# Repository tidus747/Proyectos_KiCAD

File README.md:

# Proyectos KiCAD
>Proyectos realizados en KiCAD a modo de tutoriales en Piensa 3D.

En este repositorio se almacenarán todos los proyectos para KiCAD desarrollados en Piensa 3D. Puedes encontrar todo lo necesario dentro de las carpetas con el nombre de cada uno de los proyectos. Recuerda que en si quieres subir tu proyecto a este repositorio no tienes más que enviar un mail a piensa3d.dudas@gmail.com.

## Herramientas utilizadas

Las herramientas utilizadas durante el desarrollo de los tutoriales han sido las siguientes:

- [KiCAD](http://kicad.org/) -  Suite de diseño electrónico.

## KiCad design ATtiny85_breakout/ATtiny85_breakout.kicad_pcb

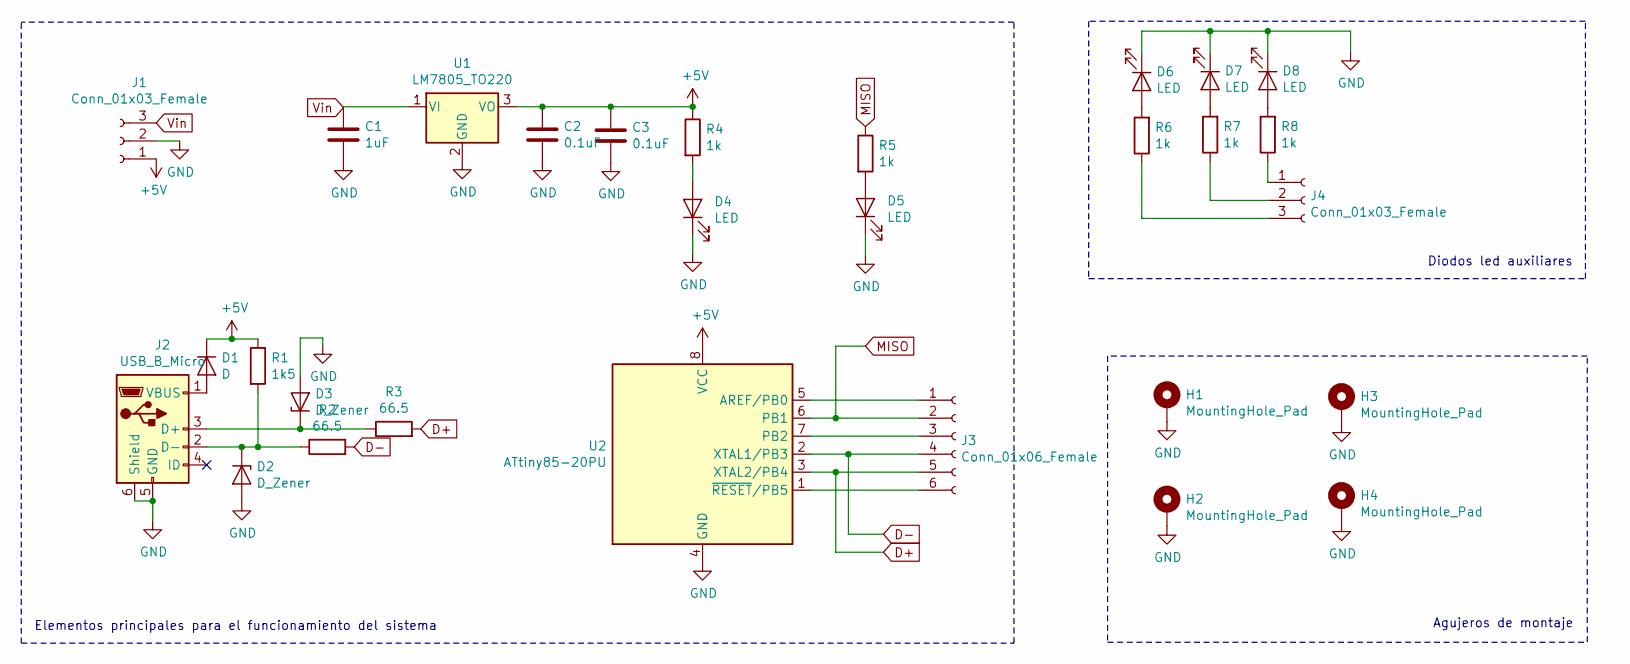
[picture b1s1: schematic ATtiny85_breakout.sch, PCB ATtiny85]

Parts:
C1: 1uF; C_Disc_D7.0mm_W2.5mm_P5.00mm
C2, C3: 0.1uF; C_Disc_D7.0mm_W2.5mm_P5.00mm
D1: D; D_A-405_P12.70mm_Horizontal
D2, D3: D_Zener; D_A-405_P7.62mm_Horizontal
D4, D5, D6, D7, D8: LED; LED_D3.0mm
H1, H2, H3, H4: MountingHole_Pad; MountingHole_2.2mm_M2
J1, J4: Conn_01x03_Female; PinHeader_1x03_P2.54mm_Vertical
J2: USB_B_Micro; USB_Micro-B_Molex_47346-0001
J3: Conn_01x06_Female; PinHeader_1x06_P2.54mm_Vertical
R1: 1k5; R_Axial_DIN0309_L9.0mm_D3.2mm_P20.32mm_Horizontal
R2, R3: 66.5; R_Axial_DIN0309_L9.0mm_D3.2mm_P20.32mm_Horizontal
R4, R5, R6, R7, R8: 1k; R_Axial_DIN0309_L9.0mm_D3.2mm_P20.32mm_Horizontal
U1: LM7805_TO220; TO-220-3_Vertical
U2: ATtiny85-20PU; DIP-8_W7.62mm

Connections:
+5V: C2.1, C3.1, D1.1 (K), J1.1, R1.1, R4.1, U1.3 (VO), U2.8 (VCC)
D+: J3.5, R3.2, U2.3 (XTAL2/PB4)
D-: J3.4, R2.2, U2.2 (XTAL1/PB3)
GND: C1.2, C2.2, C3.2, D2.2 (A), D3.2 (A), D4.1 (K), D5.1 (K), D6.1 (K), D7.1 (K), D8.1 (K), H1.1, H2.1, H3.1, H4.1, J1.2, J2.5 (GND), J2.6 (Shield), U1.2 (GND), U2.4 (GND)
MISO: J3.2, R5.1, U2.6 (PB1)
unnamed: D1.2 (A), J2.1 (VBUS)
unnamed: D2.1 (K), J2.2 (D-), R1.2, R2.1
unnamed: D3.1 (K), J2.3 (D+), R3.1
unnamed: D4.2 (A), R4.2
unnamed: D5.2 (A), R5.2
unnamed: D6.2 (A), R6.2
unnamed: D7.2 (A), R7.2
unnamed: D8.2 (A), R8.2
unnamed: J3.1, U2.5 (AREF/PB0)
unnamed: J3.3, U2.7 (PB2)
unnamed: J3.6, U2.1 (~RESET~/PB5)
unnamed: J4.1, R8.1
unnamed: J4.2, R7.1
unnamed: J4.3, R6.1
Vin: C1.1, J1.3, U1.1 (VI)

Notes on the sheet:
Elementos principales para el funcionamiento del sistema
Diodos led auxiliares
Agujeros de montaje

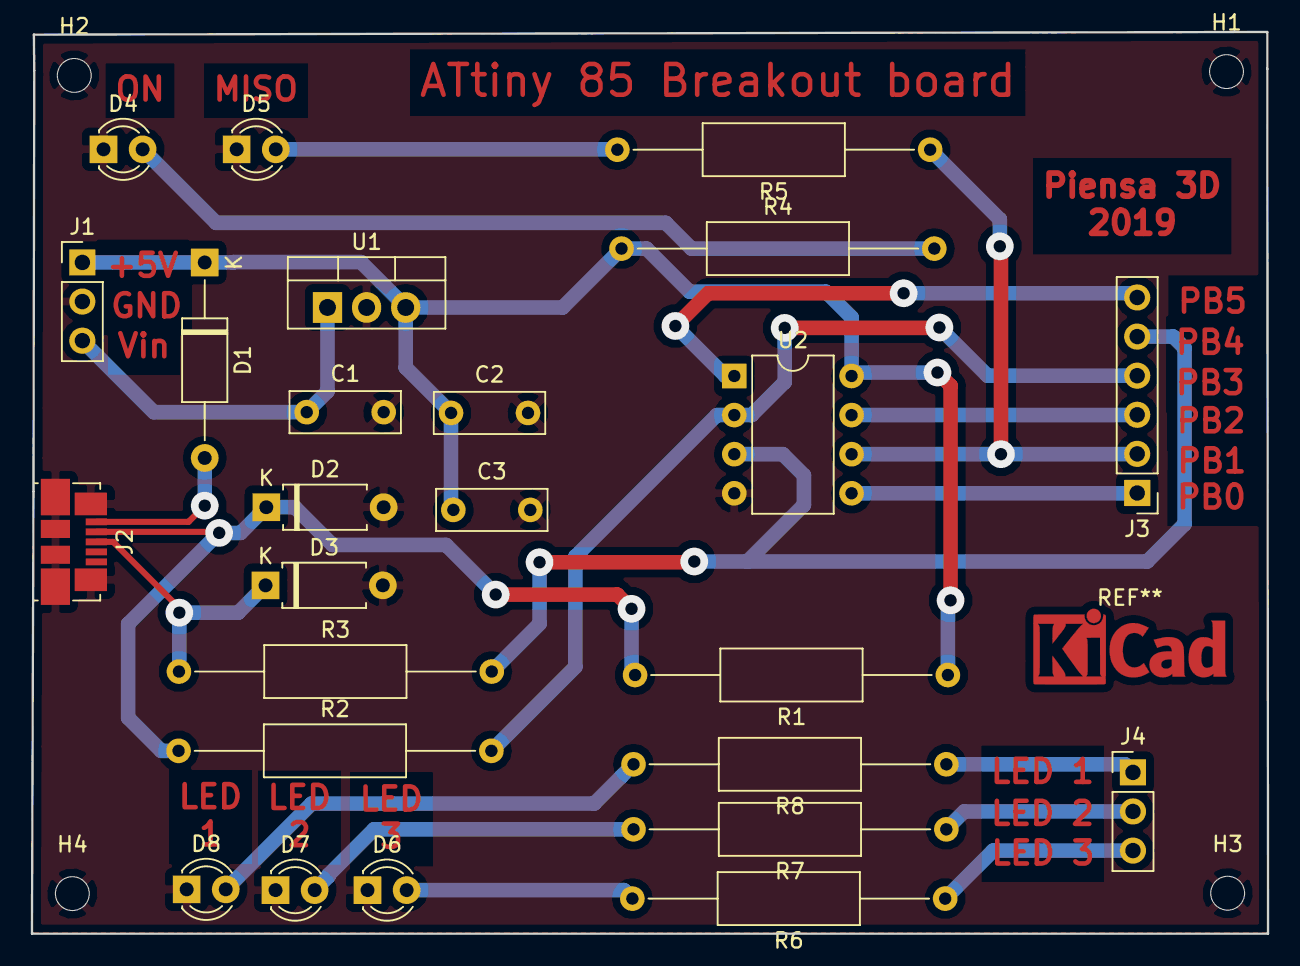
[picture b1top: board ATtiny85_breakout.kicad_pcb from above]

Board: 2 copper layers, 80.3 x 58.6 mm, 29 parts (0 on the bottom side), 20 nets.

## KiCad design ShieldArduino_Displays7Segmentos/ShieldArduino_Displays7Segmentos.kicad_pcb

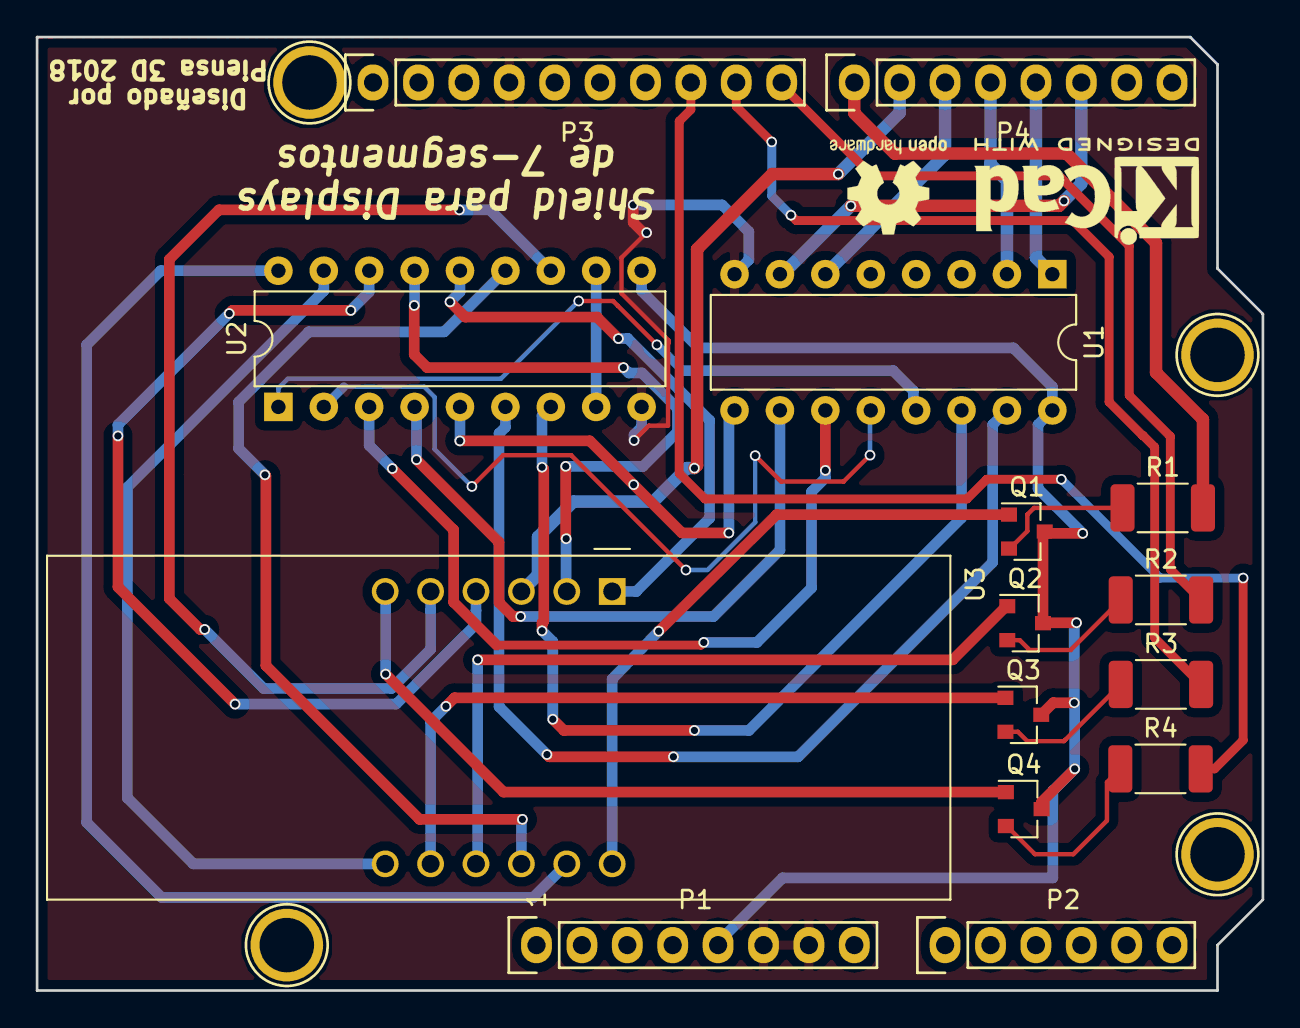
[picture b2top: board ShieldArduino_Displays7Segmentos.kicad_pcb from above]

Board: 2 copper layers, 68.6 x 53.3 mm, 19 parts (0 on the bottom side), 35 nets.

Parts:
P1: Power; Socket_Strip_Arduino_1x08
P2: Analog; Socket_Strip_Arduino_1x06
P3: Digital; Socket_Strip_Arduino_1x10
P4: Digital; Socket_Strip_Arduino_1x08
P5, P6, P7, P8: CONN_01X01; Arduino_1pin
Q1, Q2, Q3, Q4: 2N2219; SOT-23
R1, R2, R3, R4: 10k; R_2010_5025Metric
U1: 74LS247; DIP-16_W7.62mm
U2: ULN2803A; DIP-18_W7.62mm
U3: CA56-12EWA

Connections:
+5V: P1.5, Q1.3, Q2.3, Q3.3, Q4.3, U1.16, U2.10
/2: P4.6, U1.7
/3(**): P4.5, U1.1
/4: P4.4, U1.2
/5(**): P4.3, U1.6
/6(**): P4.2, U3.3
/7: P4.1, R1.2
/8: P3.10, R2.2
/9(**): P3.9, R3.2
/10(**/SS): P3.8, R4.2
/A4(SDA): P2.5, P3.2
/A5(SCL): P2.6, P3.1
GND: P1.6, P1.7, P3.4, U1.8, U2.9
unnamed: Q1.1, U3.12
unnamed: Q1.2, R1.1
unnamed: Q2.1, U3.9
unnamed: Q2.2, R2.1
unnamed: Q3.1, U3.8
unnamed: Q3.2, R3.1
unnamed: Q4.1, U3.6
unnamed: Q4.2, R4.1
unnamed: U1.9, U2.5
unnamed: U1.10, U2.4
unnamed: U1.11, U2.3
unnamed: U1.12, U2.2
unnamed: U1.13, U2.1
unnamed: U1.14, U2.7
unnamed: U1.15, U2.6
unnamed: U2.12, U3.5
unnamed: U2.13, U3.10
unnamed: U2.14, U3.1
unnamed: U2.15, U3.2
unnamed: U2.16, U3.4
unnamed: U2.17, U3.7
unnamed: U2.18, U3.11

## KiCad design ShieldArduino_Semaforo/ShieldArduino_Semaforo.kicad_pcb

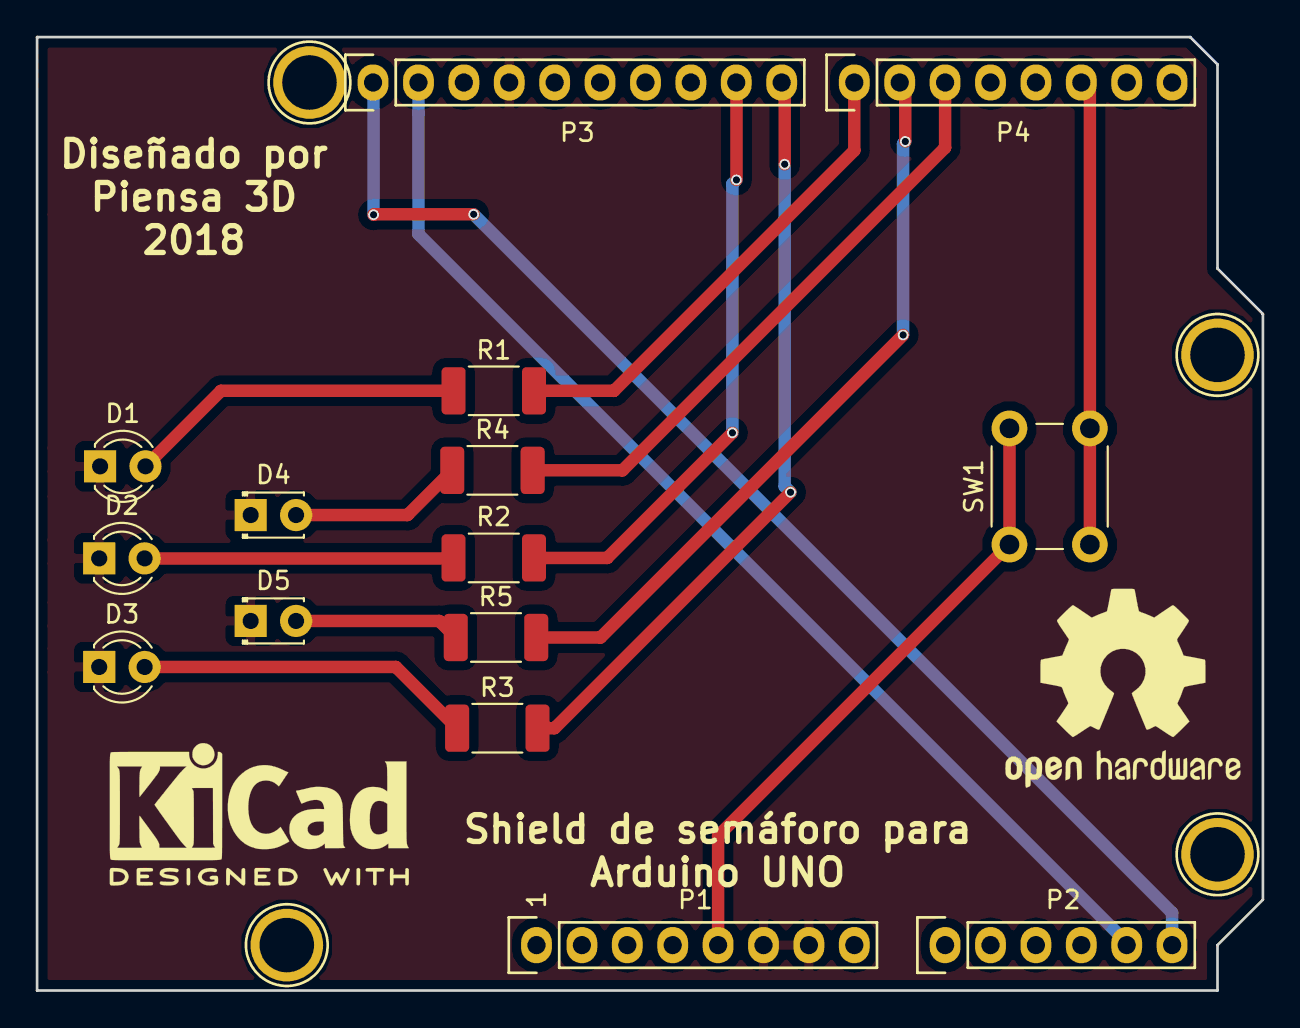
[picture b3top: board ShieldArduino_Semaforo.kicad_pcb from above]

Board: 2 copper layers, 68.6 x 53.3 mm, 19 parts (0 on the bottom side), 15 nets.

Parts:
D1, D2, D3: LED; LED_D3.0mm
D4, D5: LED; LED_D1.8mm_W3.3mm_H2.4mm
P1: Power; Socket_Strip_Arduino_1x08
P2: Analog; Socket_Strip_Arduino_1x06
P3: Digital; Socket_Strip_Arduino_1x10
P4: Digital; Socket_Strip_Arduino_1x08
P5, P6, P7, P8: CONN_01X01; Arduino_1pin
R1, R2, R3, R4, R5: R; R_2010_5025Metric
SW1: SW_Push; SW_PUSH_6mm

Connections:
+5V: P1.5, SW1.1
/2: P4.6, SW1.2
/5(**): P4.3, R4.2
/6(**): P4.2, R5.2
/7: P4.1, R1.2
/8: P3.10, R3.2
/9(**): P3.9, R2.2
/A4(SDA): P2.5, P3.2
/A5(SCL): P2.6, P3.1
GND: D1.1, D2.1, D3.1, D4.1, D5.1, P1.6, P1.7, P3.4
unnamed: D1.2, R1.1
unnamed: D2.2, R2.1
unnamed: D3.2, R3.1
unnamed: D4.2, R4.1
unnamed: D5.2, R5.1

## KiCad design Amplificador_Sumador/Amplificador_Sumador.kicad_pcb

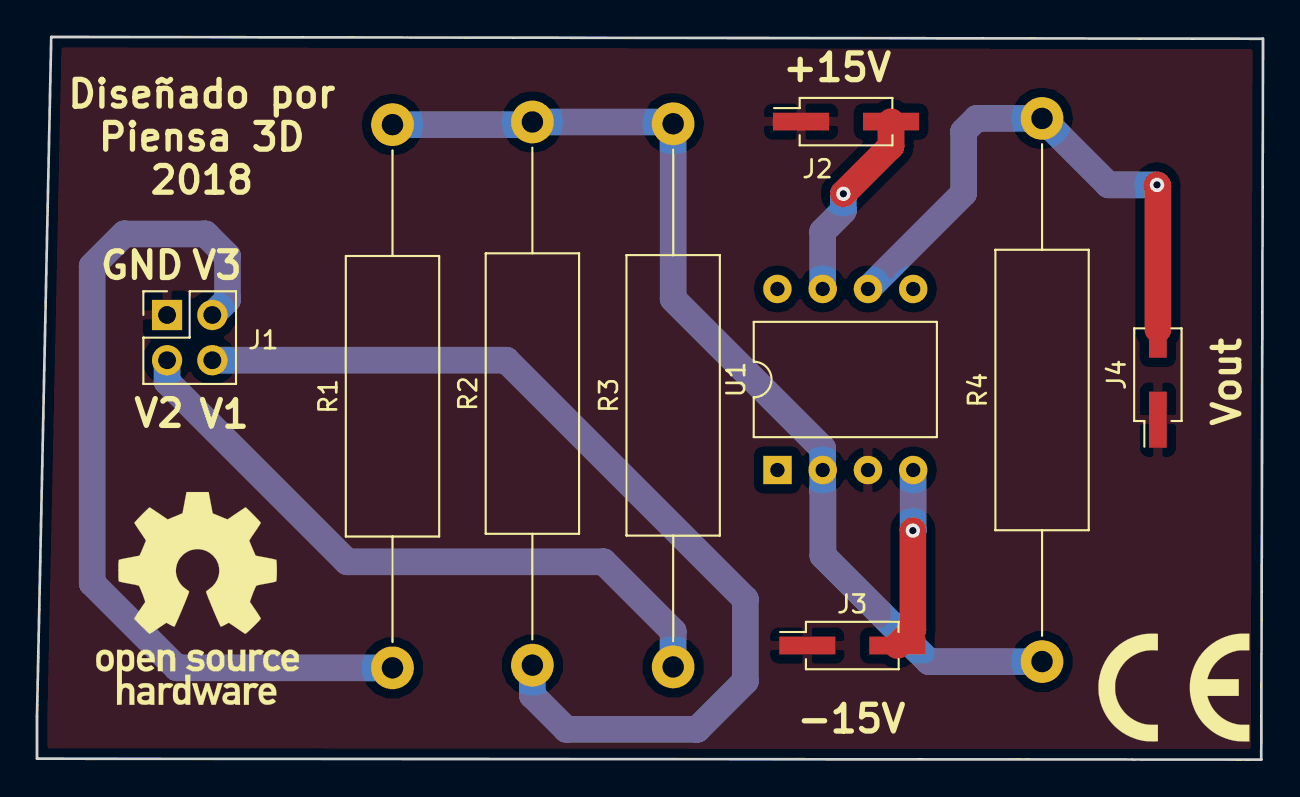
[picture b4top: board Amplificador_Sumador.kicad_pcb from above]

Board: 2 copper layers, 68.8 x 40.5 mm, 9 parts (0 on the bottom side), 8 nets.

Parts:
J1: Conn_01x04_Male; PinHeader_2x02_P2.54mm_Vertical
J2, J3, J4: Conn_01x02_Male; PinHeader_2x01_P2.54mm_Vertical_SMD
R1, R2, R3, R4: 1k; R_Axial_DIN0516_L15.5mm_D5.0mm_P30.48mm_Horizontal
U1: LM741; DIP-8_W10.16mm

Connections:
+15V: J2.2, U1.7
-15V: J3.2, U1.4
GND: J1.1, J2.1, J3.1, J4.1, U1.3
unnamed: J1.2, R1.1
unnamed: J1.3, R3.1
unnamed: J1.4, R2.1
unnamed: J4.2, R4.2, U1.6
unnamed: R1.2, R2.2, R3.2, R4.1, U1.2

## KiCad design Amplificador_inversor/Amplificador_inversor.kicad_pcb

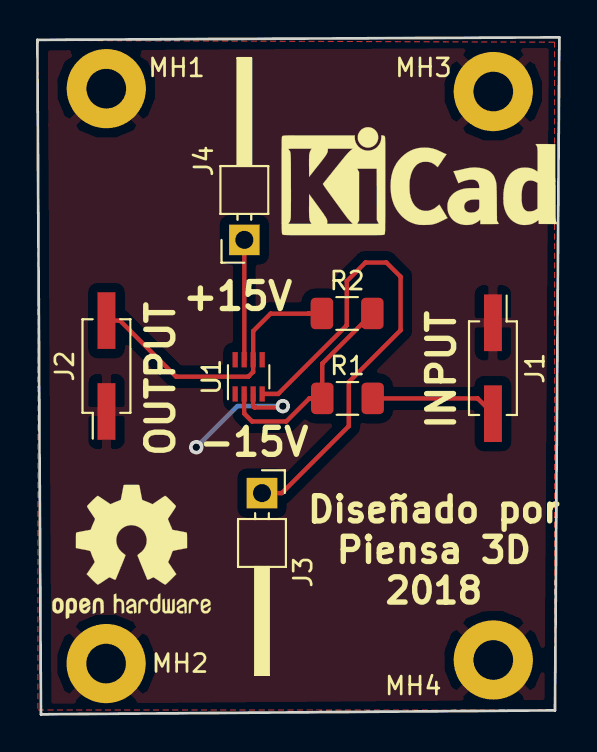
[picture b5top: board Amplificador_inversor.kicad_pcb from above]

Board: 2 copper layers, 29.0 x 37.6 mm, 11 parts (0 on the bottom side), 6 nets.

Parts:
J1, J2: Conn_01x02_Male; PinHeader_2x01_P2.54mm_Vertical_SMD
J3, J4: Conn_01x01_Male; PinHeader_1x01_P2.54mm_Horizontal
MH1, MH2, MH3, MH4: MountingHole_Pad; MountingHole_2.2mm_M2_Pad
R1: 1k; R_1206_3216Metric
R2: 4k; R_1206_3216Metric
U1: LM741; DFN-8_2x2mm_P0.5mm

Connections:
+15V: J4.1, U1.7
-15V: J3.1, U1.4
GND: J1.1, J2.1, MH1.1, MH2.1, MH3.1, MH4.1, U1.3
unnamed: J1.2, R1.2
unnamed: J2.2, R2.1, U1.6
unnamed: R1.1, R2.2, U1.2

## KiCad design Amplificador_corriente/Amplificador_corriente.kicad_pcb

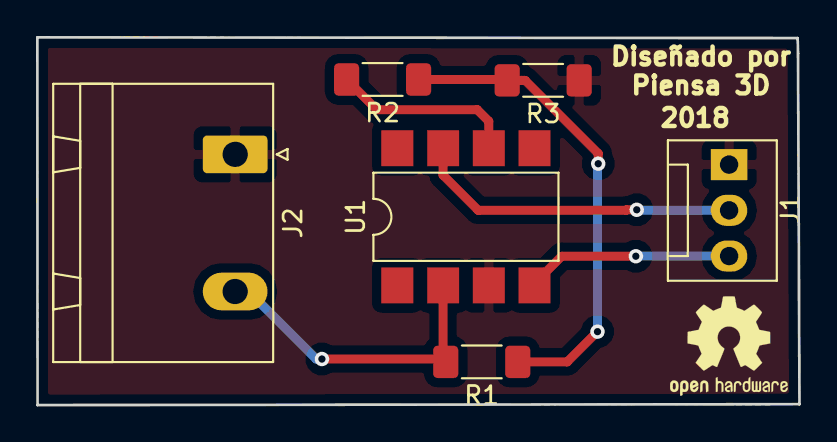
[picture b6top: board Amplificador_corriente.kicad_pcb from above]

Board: 2 copper layers, 42.3 x 20.4 mm, 6 parts (0 on the bottom side), 6 nets.

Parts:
J1: Conn_01x03_Male; FanPinHeader_1x03_P2.54mm_Vertical
J2: Conn_01x02_Male; PhoenixContact_GMSTBA_2,5_2-G-7,62_1x02_P7.62mm_Horizontal
R1: 2k; R_1806_4516Metric
R2: 100; R_1806_4516Metric
R3: 1k; R_1806_4516Metric
U1: LM741; SMDIP-8_W7.62mm

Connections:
+12V: J1.2, U1.7
-12V: J1.3, U1.4
GND: J1.1, J2.1, R3.1, U1.3
unnamed: J2.2, R1.2, U1.2
unnamed: R1.1, R2.1, R3.2
unnamed: R2.2, U1.6

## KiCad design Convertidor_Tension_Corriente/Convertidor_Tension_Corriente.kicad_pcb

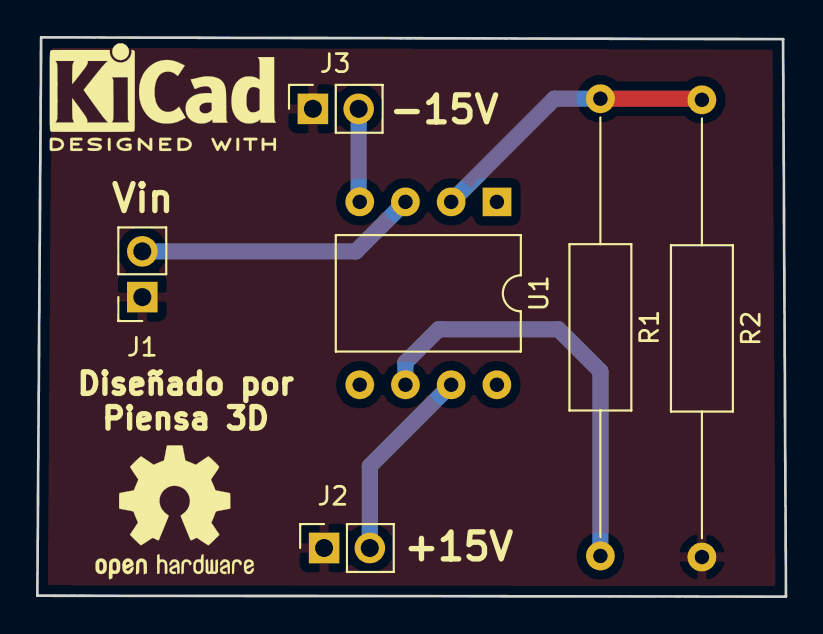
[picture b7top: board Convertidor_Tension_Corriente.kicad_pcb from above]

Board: 2 copper layers, 41.6 x 31.1 mm, 6 parts (0 on the bottom side), 6 nets.

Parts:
J1, J2, J3: Conn_01x02_Male; PinSocket_1x02_P2.54mm_Vertical
R1: RL; R_Axial_DIN0309_L9.0mm_D3.2mm_P25.40mm_Horizontal
R2: 1k; R_Axial_DIN0309_L9.0mm_D3.2mm_P25.40mm_Horizontal
U1: LM741; DIP-8_W10.16mm

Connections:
+15V: J2.2, U1.7
-15V: J3.2, U1.4
GND: J1.1, J2.1, J3.1, R2.2
unnamed: J1.2, U1.3
unnamed: R1.1, R2.1, U1.2
unnamed: R1.2, U1.6

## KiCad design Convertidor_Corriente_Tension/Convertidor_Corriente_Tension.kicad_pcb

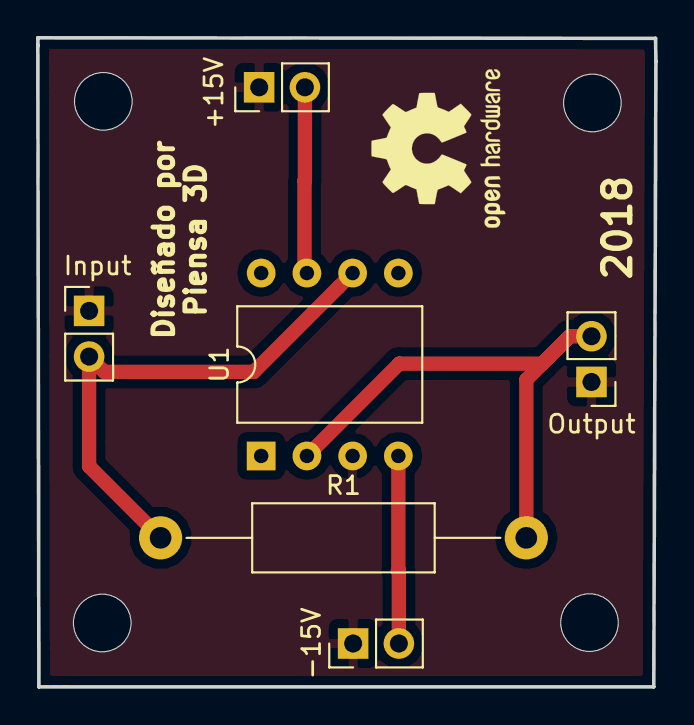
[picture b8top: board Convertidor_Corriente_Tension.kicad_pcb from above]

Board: 2 copper layers, 34.3 x 36.1 mm, 6 parts (0 on the bottom side), 5 nets.

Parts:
+15V: Conn_01x02_Male; PinHeader_1x02_P2.54mm_Vertical
-15V: Conn_01x02_Male; PinHeader_1x02_P2.54mm_Vertical
Input : Conn_01x02_Male; PinHeader_1x02_P2.54mm_Vertical
Output: Conn_01x02_Male; PinHeader_1x02_P2.54mm_Vertical
R1: 1k; R_Axial_DIN0411_L9.9mm_D3.6mm_P20.32mm_Horizontal
U1: LM741; DIP-8_W10.16mm

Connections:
+15V: +15V.2, U1.7
-15V: -15V.2, U1.4
GND: +15V.1, -15V.1, Input.1, Output.1, U1.3
unnamed: Output.2, R1.2, U1.2
unnamed: Input.2, R1.1, U1.6

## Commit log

2018-02-11 Añadimos el proyecto de regulador de tensión
2018-02-14 Añadimos la versión 1.1 del regulador
2018-02-16 Añadimos el título al readme
2018-02-16 Completamos el readme
2018-08-23 Añadimos el proyecto de la Arduino Nano Board
2018-09-02 Añadimos el regulador de tensión
2018-09-02 Añadimos el amplificador en configuración no inversora
2018-09-03 Añadimos el proyecto de convertidor de corriente tensión
2018-09-17 Añadimos el proyecto del convertidor de tensión a corriente
2018-09-20 Añadimos el tutorial del amplificador de corriente
2018-09-25 Añadimnos el proyecto del amplificador inversor
2018-09-26 Corregimos un error en el README
2018-09-27 Añadimos el proyecto del amplificador sumador
2018-10-09 Añadimos el shield de semáforo de Arduino UNO
2018-10-11 Añadimos el shield con los displays de 7 segmentos
2019-01-16 Añadimos el proyecto del ATtiny85
2019-01-16 Añadimos los ficheros de fabricación
2019-01-18 Añadimos modificaciones en el diseño
2021-11-10 Update README.md
    https://forum.kicad.info/t/warning-avoid-all-links-to-kicad-pcb-org-use-kicad-org/31521
